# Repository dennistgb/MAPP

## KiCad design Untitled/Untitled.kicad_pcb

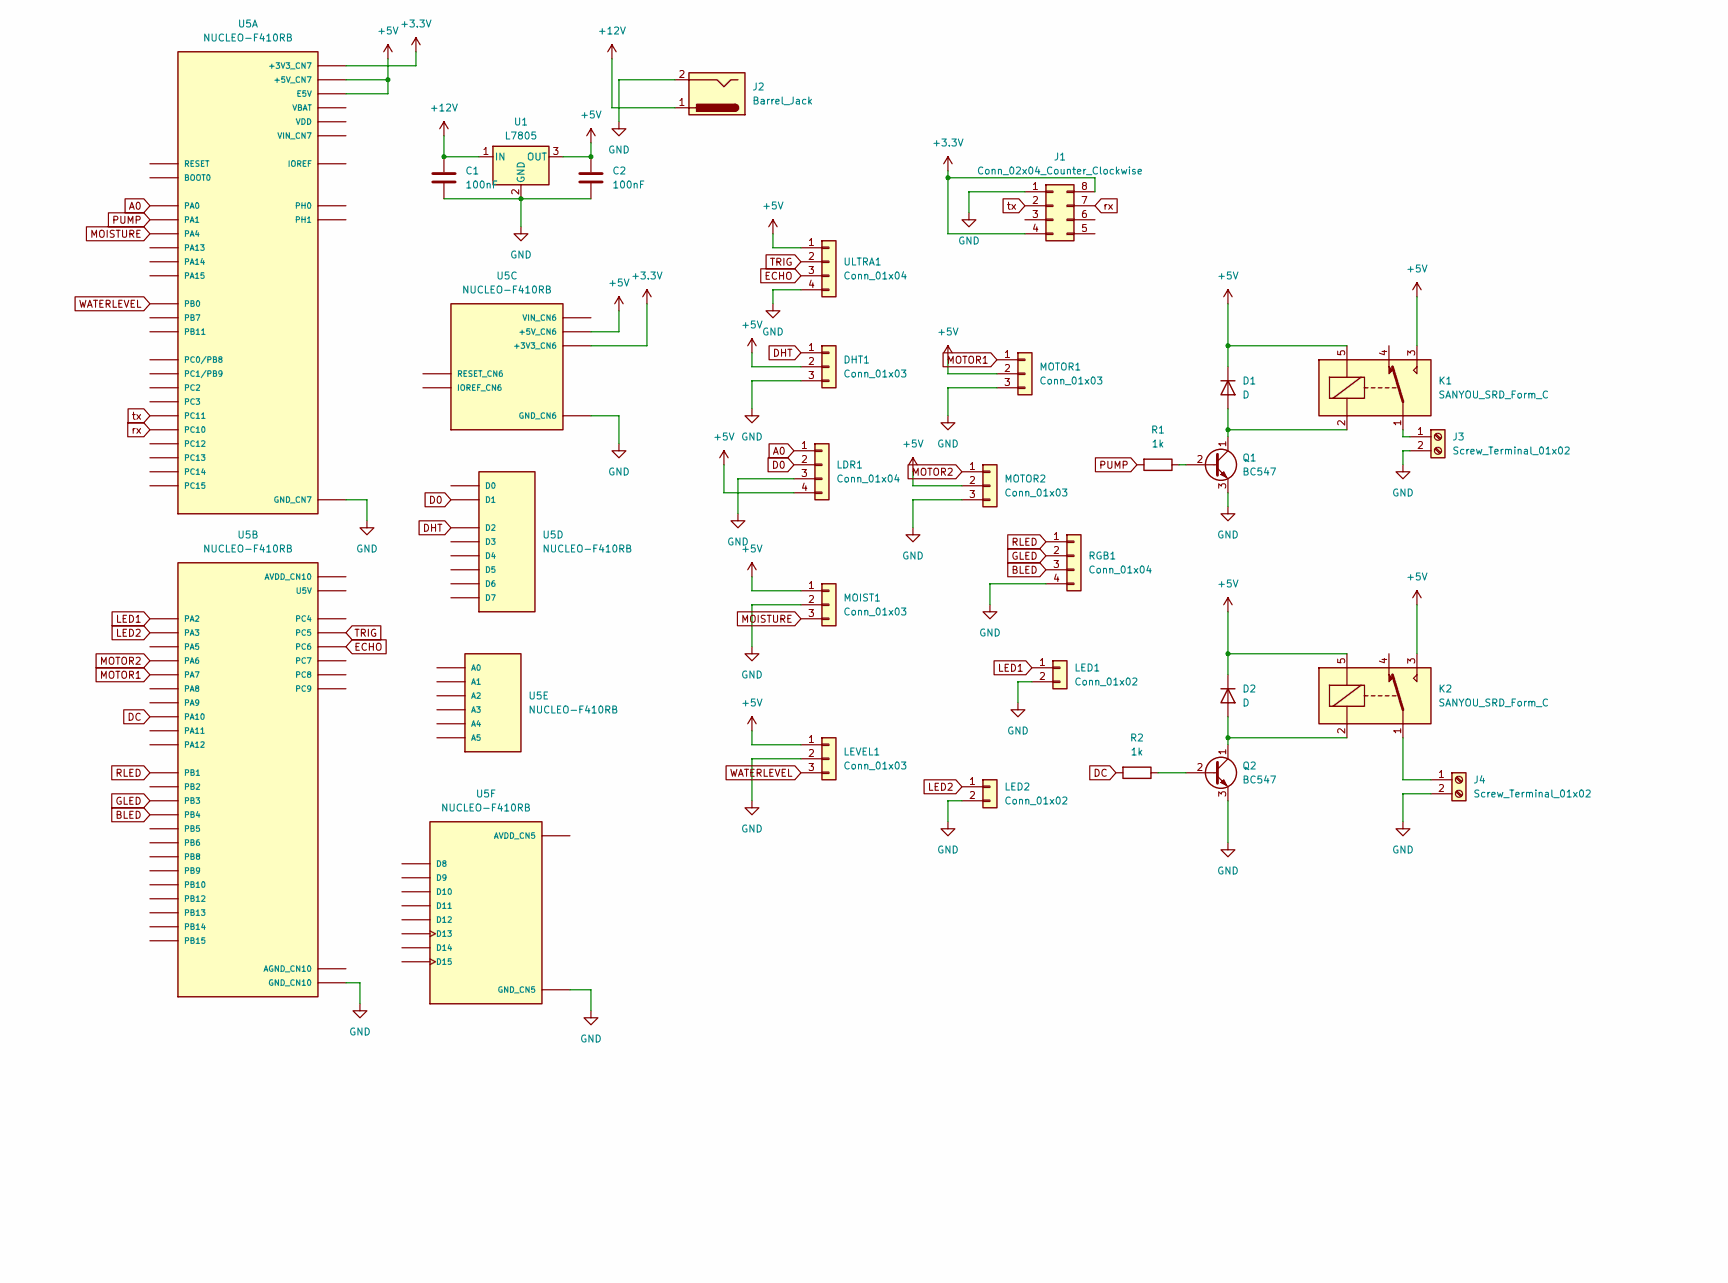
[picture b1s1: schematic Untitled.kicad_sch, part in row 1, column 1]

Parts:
C1, C2: 100nF; C_Axial_L3.8mm_D2.6mm_P7.50mm_Horizontal
D1, D2: D; D_A-405_P10.16mm_Horizontal
DHT1: Conn_01x03; PinHeader_1x03_P2.54mm_Vertical
J1: Conn_02x04_Counter_Clockwise; PinHeader_2x04_P2.54mm_Vertical
J2: Barrel_Jack; BarrelJack_Kycon_KLDX-0202-xC_Horizontal
J3, J4: Screw_Terminal_01x02; TerminalBlock_MetzConnect_Type011_RT05502HBWC_1x02_P5.00mm_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
K1, K2: SANYOU_SRD_Form_C; Relay_SPDT_SANYOU_SRD_Series_Form_C
LDR1: Conn_01x04; PinHeader_1x04_P2.54mm_Vertical
LED1, LED2: Conn_01x02; PinHeader_1x02_P2.54mm_Vertical
LEVEL1: Conn_01x03; PinHeader_1x03_P2.54mm_Vertical
MOIST1: Conn_01x03; PinHeader_1x03_P2.54mm_Vertical
MOTOR1, MOTOR2: Conn_01x03; PinHeader_1x03_P2.54mm_Vertical
Q1, Q2: BC547; TO-92_Inline
R1, R2: 1k; R_Axial_DIN0207_L6.3mm_D2.5mm_P10.16mm_Horizontal
RGB1: Conn_01x04; PinHeader_1x04_P2.54mm_Vertical
U1: L7805; TO-252-2
U5: NUCLEO-F410RB; ST_NUCLEO-F410RB; PARTREV 13
ULTRA1: Conn_01x04; PinHeader_1x04_P2.54mm_Vertical

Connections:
+3.3V: J1.4, J1.8, U5.CN6_4 (+3V3_CN6), U5.CN7_16 (+3V3_CN7)
+5V: C2.1, D1.1 (K), D2.1 (K), DHT1.2, K1.3, K1.5, K2.3, K2.5, LDR1.4, LEVEL1.1, MOIST1.1, MOTOR1.2, MOTOR2.2, U1.3 (OUT), U5.CN6_5 (+5V_CN6), U5.CN7_6 (E5V), U5.CN7_18 (+5V_CN7), ULTRA1.1
+12V: C1.1, J2.1, U1.1 (IN)
A0: LDR1.1, U5.CN7_28 (PA0)
BLED: RGB1.3, U5.CN10_27 (PB4)
D0: LDR1.2, U5.CN9_2 (D1)
DC: R2.2, U5.CN10_33 (PA10)
DHT: DHT1.1, U5.CN9_3 (D2)
ECHO: U5.CN10_4 (PC6), ULTRA1.3
GLED: RGB1.2, U5.CN10_31 (PB3)
GND: C1.2, C2.2, DHT1.3, J1.1, J2.2, J3.2, J4.2, LDR1.3, LED1.2, LED2.2, LEVEL1.2, MOIST1.2, MOTOR1.3, MOTOR2.3, Q1.3 (E), Q2.3 (E), RGB1.4, U1.2 (GND), U5.CN5_7 (GND_CN5), U5.CN6_6 (GND_CN6), U5.CN6_7 (GND_CN6), U5.CN7_8 (GND_CN7), U5.CN7_19 (GND_CN7), U5.CN7_20 (GND_CN7), U5.CN7_22 (GND_CN7), U5.CN10_9 (GND_CN10), U5.CN10_20 (GND_CN10), ULTRA1.4
LED1: LED1.1, U5.CN10_35 (PA2)
LED2: LED2.1, U5.CN10_37 (PA3)
MOISTURE: MOIST1.3, U5.CN7_32 (PA4)
MOTOR1: MOTOR1.1, U5.CN10_15 (PA7)
MOTOR2: MOTOR2.1, U5.CN10_13 (PA6)
unnamed: D1.2 (A), K1.2, Q1.1 (C)
unnamed: D2.2 (A), K2.2, Q2.1 (C)
unnamed: J3.1, K1.1
unnamed: J4.1, K2.1
unnamed: Q1.2 (B), R1.1
unnamed: Q2.2 (B), R2.1
PUMP: R1.2, U5.CN7_30 (PA1)
RLED: RGB1.1, U5.CN10_24 (PB1)
TRIG: U5.CN10_6 (PC5), ULTRA1.2
WATERLEVEL: LEVEL1.3, U5.CN7_34 (PB0)
rx: J1.7, U5.CN7_1 (PC10)
tx: J1.2, U5.CN7_2 (PC11)

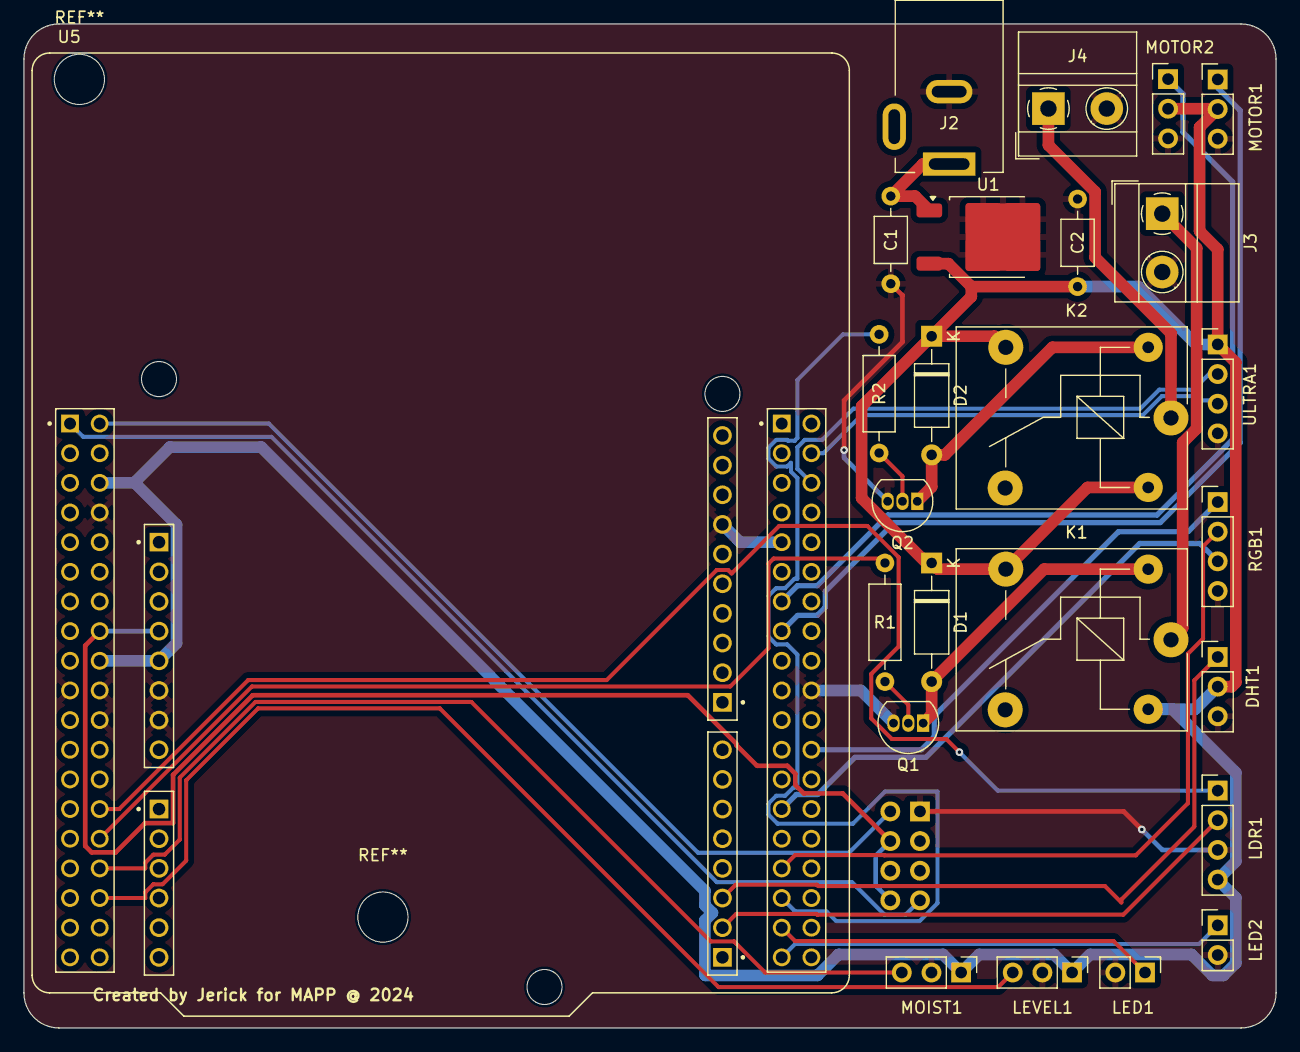
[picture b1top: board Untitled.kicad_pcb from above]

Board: 2 copper layers, 107.2 x 86.0 mm, 26 parts (1 on the bottom side), 28 nets.

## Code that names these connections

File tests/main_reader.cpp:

#include <cstdio>
#undef __ARM_FP
#include "mbed.h"
#include "DHT11.h"
#include <chrono>
using namespace std::chrono;

#define WAIT_TIME_MS_0 500
#define WAIT_TIME_MS_1 1500
// Timeout duration for no object detection
#define ECHO_TIME_OUT 30ms
//Timer for fish feeder
#define INTERVAL 10
//defitions for fish feeder
#define WAIT_TIME_MS 2000          // Sleep time to allow motor to turn
#define PERIOD_WIDTH 20            // Period in ms according to the servo motor datasheet
#define PULSE_WIDTH_90_DEGREE 2400 // Pulse width in us to move to 90 degree position
#define PULSE_WIDTH_0_DEGREE 1500  // Pulse width in us to move to 0 position
#define PULSE_WIDTH_N_90_DEGREE 600 // Pulse width in us to move to -90 degree position

//Grow light Pin
DigitalOut GrowLight(PA_2);

//Warning system (RGB LED) pins
DigitalOut redPin(PB_1);      
DigitalOut greenPin(PB_3); 
DigitalOut bluePin(PB_4); 

// moisture sensor analog pin 
AnalogIn MoistureSensor(PA_4);

//relay to control water pump
DigitalOut relay(PA_1);     

// water level analog pin
AnalogIn water_level(PB_0); 
DigitalIn LDRSensor_DO(PD_1);
AnalogIn LDRSensor_AO(PA_0);

//ultrasound pins
DigitalOut Trig(PC_5);   // Trigger Pin
InterruptIn Echo(PC_6);  // Echo Pin with interrupt
//timers for utlrasound
Timer echoTimer;         // Timer to measure duration
Timeout echoTimeout;     // Timeout handler

// servo motor pins for fish feeder
PwmOut motor(PA_7);
//ticker for fish feeder
Ticker feederTicker;
Timer feederTimer;

//dht pin
DHT11 dht11(PD_2);

float Moist = 0;
float Water_level = 0;
float objDistance = 0;
bool bObjDetected = false;
float LDR_AO_voltage = 0.0;

// ISR for Echo timeout
void ISR_EchoTimeout() 
{
    printf("Timeout: No obstacle detected!\n");
}
// ISR for rising edge (start of Echo signal)
void ISR_EchoHigh()
{
    echoTimer.reset();
    echoTimeout.attach(&ISR_EchoTimeout, ECHO_TIME_OUT);  // Attach timeout handler
}
// ISR for falling edge (end of Echo signal)
void ISR_EchoLow() 
{
    bObjDetected = true;
    echoTimeout.detach();  // Cancel timeout
    float duration = duration_cast<microseconds>(echoTimer.elapsed_time()).count();
    objDistance = (0.03432 * duration) / 2;  // Calculate distance in cm
}

// Function to measure distance using the ultrasonic sensor
float get_distance()
{
    // Send a 10us pulse to the Trigger pin
    Trig = 1;
    wait_us(10);
    Trig = 0;

    // Wait for Echo response
    echoTimer.start();
    while (!Echo.read())  // Wait for rising edge
    {
        if (echoTimer.elapsed_time() > ECHO_TIME_OUT)
        {
            echoTimer.stop();
            echoTimer.reset();
            return -1;  // Timeout, no object detected
        }
    }

    echoTimer.reset();
    echoTimer.start();
    while (Echo.read())  // Wait for falling edge
    {
        if (echoTimer.elapsed_time() > ECHO_TIME_OUT)
        {
            echoTimer.stop();
            echoTimer.reset();
            return -1;  // Timeout, no object detected
        }
    }

    echoTimer.stop();
    float duration = duration_cast<microseconds>(echoTimer.elapsed_time()).count();
    return (0.03432 * duration) / 2;  // Calculate distance in cm
}

// Function to get the temperature using DHT
int get_temp()
{
    int temperature = dht11.readTemperature();
    if (temperature != DHT11::ERROR_CHECKSUM && temperature != DHT11::ERROR_TIMEOUT)
    {
        return temperature; 
    }
    else
    {
        printf("%s\n", dht11.getErrorString(temperature)); 
        return -1; 
    }
}

// Function to get the humidity using DHT
int get_humidity()
{
    int humidity = dht11.readHumidity();
    if (humidity != DHT11::ERROR_CHECKSUM && humidity != DHT11::ERROR_TIMEOUT)
    {
        return humidity; 
    }
    else
    {
        printf("%s\n", dht11.getErrorString(humidity)); 
        return -1; 
    }
}

//Function to get brightness using LDR
int get_brightness()
{
    LDR_AO_voltage = LDRSensor_AO.read();
    LDR_AO_voltage = LDR_AO_voltage * 3.3;
    return LDR_AO_voltage;
}

void pump_water()
{
    relay = 1;
    thread_sleep_for(5000);
    relay = 0;
}

void start_feeder()
{
    motor.period_ms(PERIOD_WIDTH);                   // Set the period according to the servo specification
    motor.pulsewidth_us(PULSE_WIDTH_0_DEGREE);       // Move to 0 position (middle)
    printf("Move to 0 position: Middle\n");

    feederTimer.reset();  // Reset the timer
    feederTimer.start();  // Start the timer
    while (feederTimer.elapsed_time() < std::chrono::milliseconds(WAIT_TIME_MS)) // Wait until the time elapses
    {
        // Optionally, you can add other code here to do something during the waiting time
    }

    motor.pulsewidth_us(PULSE_WIDTH_90_DEGREE);      // Move to 90 degree (right)
    printf("Move to 90 degree position: Right\n");

    feederTimer.reset();  // Reset the timer for the next wait period
    feederTimer.start();  // Start the timer
    while (feederTimer.elapsed_time() < std::chrono::milliseconds(WAIT_TIME_MS)) // Wait until the time elapses
    {
        // Optionally, you can add other code here to do something during the waiting time
    }

    motor.pulsewidth_us(PULSE_WIDTH_N_90_DEGREE);    // Move to -90 degree (left)
    printf("Move to -90 degree position: Left\n");

    feederTimer.reset();  // Reset the timer for the next wait period
    feederTimer.start();  // Start the timer
    while (feederTimer.elapsed_time() < std::chrono::milliseconds(WAIT_TIME_MS)) // Wait until the time elapses
    {
        // Optionally, you can add other code here to do something during the waiting time
    }

    motor.period_ms(PERIOD_WIDTH);                   // Set the period according to the servo specification
}

int main()
{
    LDRSensor_AO.set_reference_voltage(3.3f);
    feederTicker.attach(&start_feeder, INTERVAL);
    
    while (1)
    {
        printf("Reading phase\n");
        // Temperature reading
        int temperature = get_temp();
        if (temperature != -1)
        {
            printf("Temperature: %d °C\n", temperature);
        }
        else
        {
            printf("Failed to read temperature.\n");
        }

        // Humidity reading
        int humidity = get_humidity();
        if (humidity != -1)
        {
            printf("Humidity: %d %%\n", humidity);
        }
        else
        {
            printf("Failed to read humidity.\n");
        }

        // Distance reading
        float distance = get_distance();
        if (distance != -1)
        {
            printf("Distance: %.2f cm\n", distance);
        }
        else
        {
            printf("Failed to detect distance.\n");
        }

        //brightness reading
        float brightness = get_brightness();
        printf("Brightness: %.3f V\n", brightness);

        Moist = MoistureSensor.read(); 
        printf("Soil Moisture: %.2f\n", Moist);
        
        Water_level = water_level.read(); 
        printf("Water Level: %.2f\n", Water_level);

        thread_sleep_for(1000);

        printf("Correctional phase\n");
        if (temperature == 50)
        {
            //start dc motor fan
        }
        if (humidity == 60)
        {
            //start dc motor fan
        }
        //If plant is too close (needs to be cut) put red on RGB LED
        if(distance == 10)
        {
            bluePin = 0;
            greenPin = 0;
            redPin = 1;
        }
        else 
        {
            bluePin = 0;
            greenPin = 1;
            redPin = 0;
        }
        //If brightness is too low turn on grow light
        if (brightness > 2.2)
        {
            GrowLight = 1;
        }
        else 
        {
            GrowLight = 0;
        }
        //If soil moisture too low pump water
        if (Moist == 0.95) 
        {
            pump_water();
        }
        //If water level to high, put up blue warning LED
        if (Water_level == 10)
        {
            bluePin = 1;
            greenPin = 0;
            redPin = 0;
        }
        else 
        {
            bluePin = 0;
            greenPin = 1;
            redPin = 0;
        }
    }
}

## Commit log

2025-01-13 started on server
2025-01-20 adding LCD UI code
2025-01-20 Keypad function integrated with LCD for case checking
2025-01-20 finished backend
2025-01-20 changing keypad to external hardware interrupt based
2025-01-26 Adding new file for 2nd STM (main STM) and adding DHT code
2025-01-26 Ultrasound added to reader code
2025-01-26 added moisture sensor, water pump and Water level sensor code ( moisture sensor code still not fully working )
2025-02-02 added kicad thing
2025-02-02 started work on thing
2025-02-03 added RGB LED and some other correctional phase code
2025-02-03 updated routes
2025-02-03 added back in mbed code
2025-02-03 added mbed code
2025-02-03 added paven file
2025-02-03 finished
2025-02-14 UART communication across STM working
2025-02-14 slave branch code
2025-02-14 added screenshots
2025-02-15 working wifi with STM communincation
2025-02-15 fixed keypad
2025-02-15 working
